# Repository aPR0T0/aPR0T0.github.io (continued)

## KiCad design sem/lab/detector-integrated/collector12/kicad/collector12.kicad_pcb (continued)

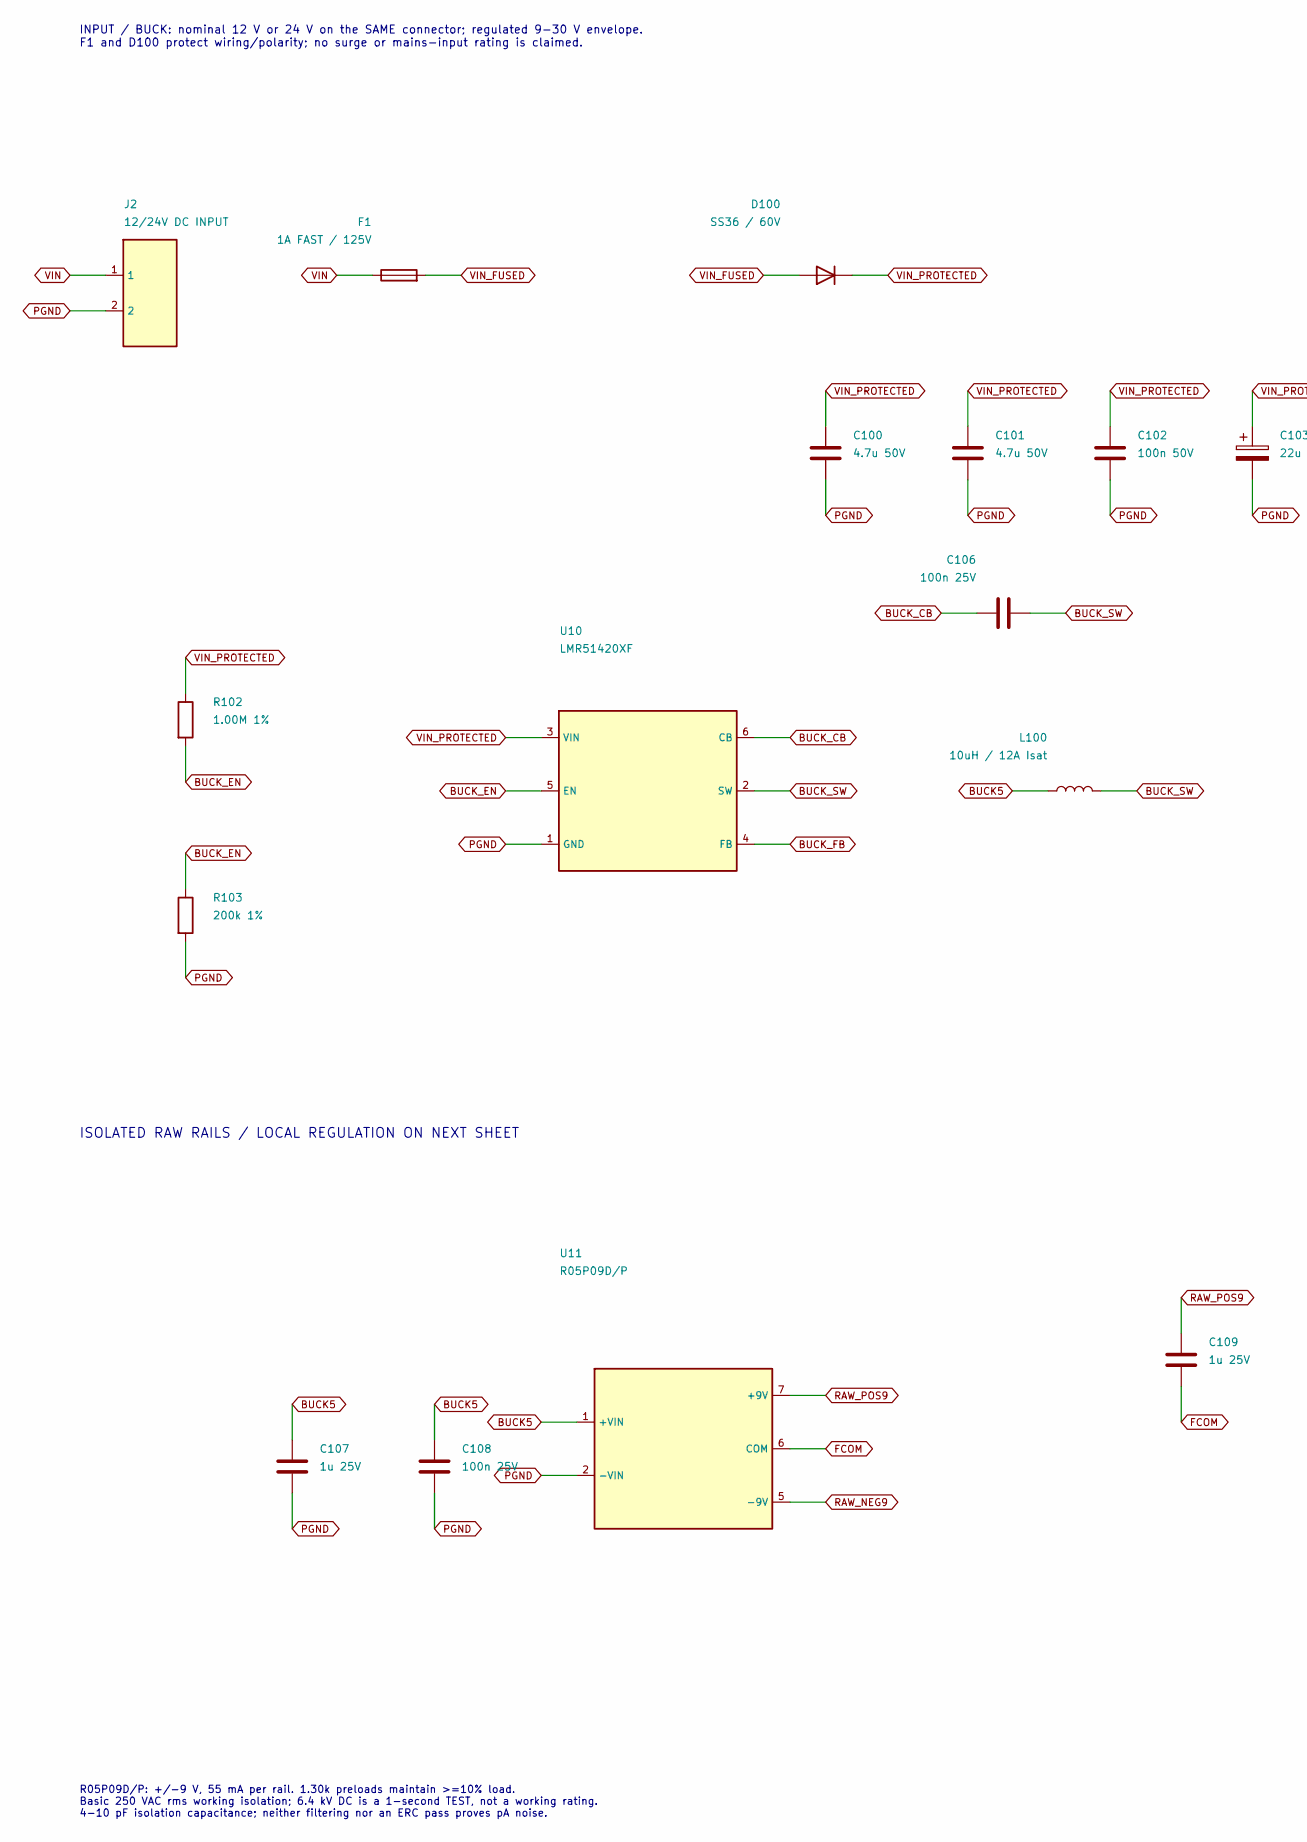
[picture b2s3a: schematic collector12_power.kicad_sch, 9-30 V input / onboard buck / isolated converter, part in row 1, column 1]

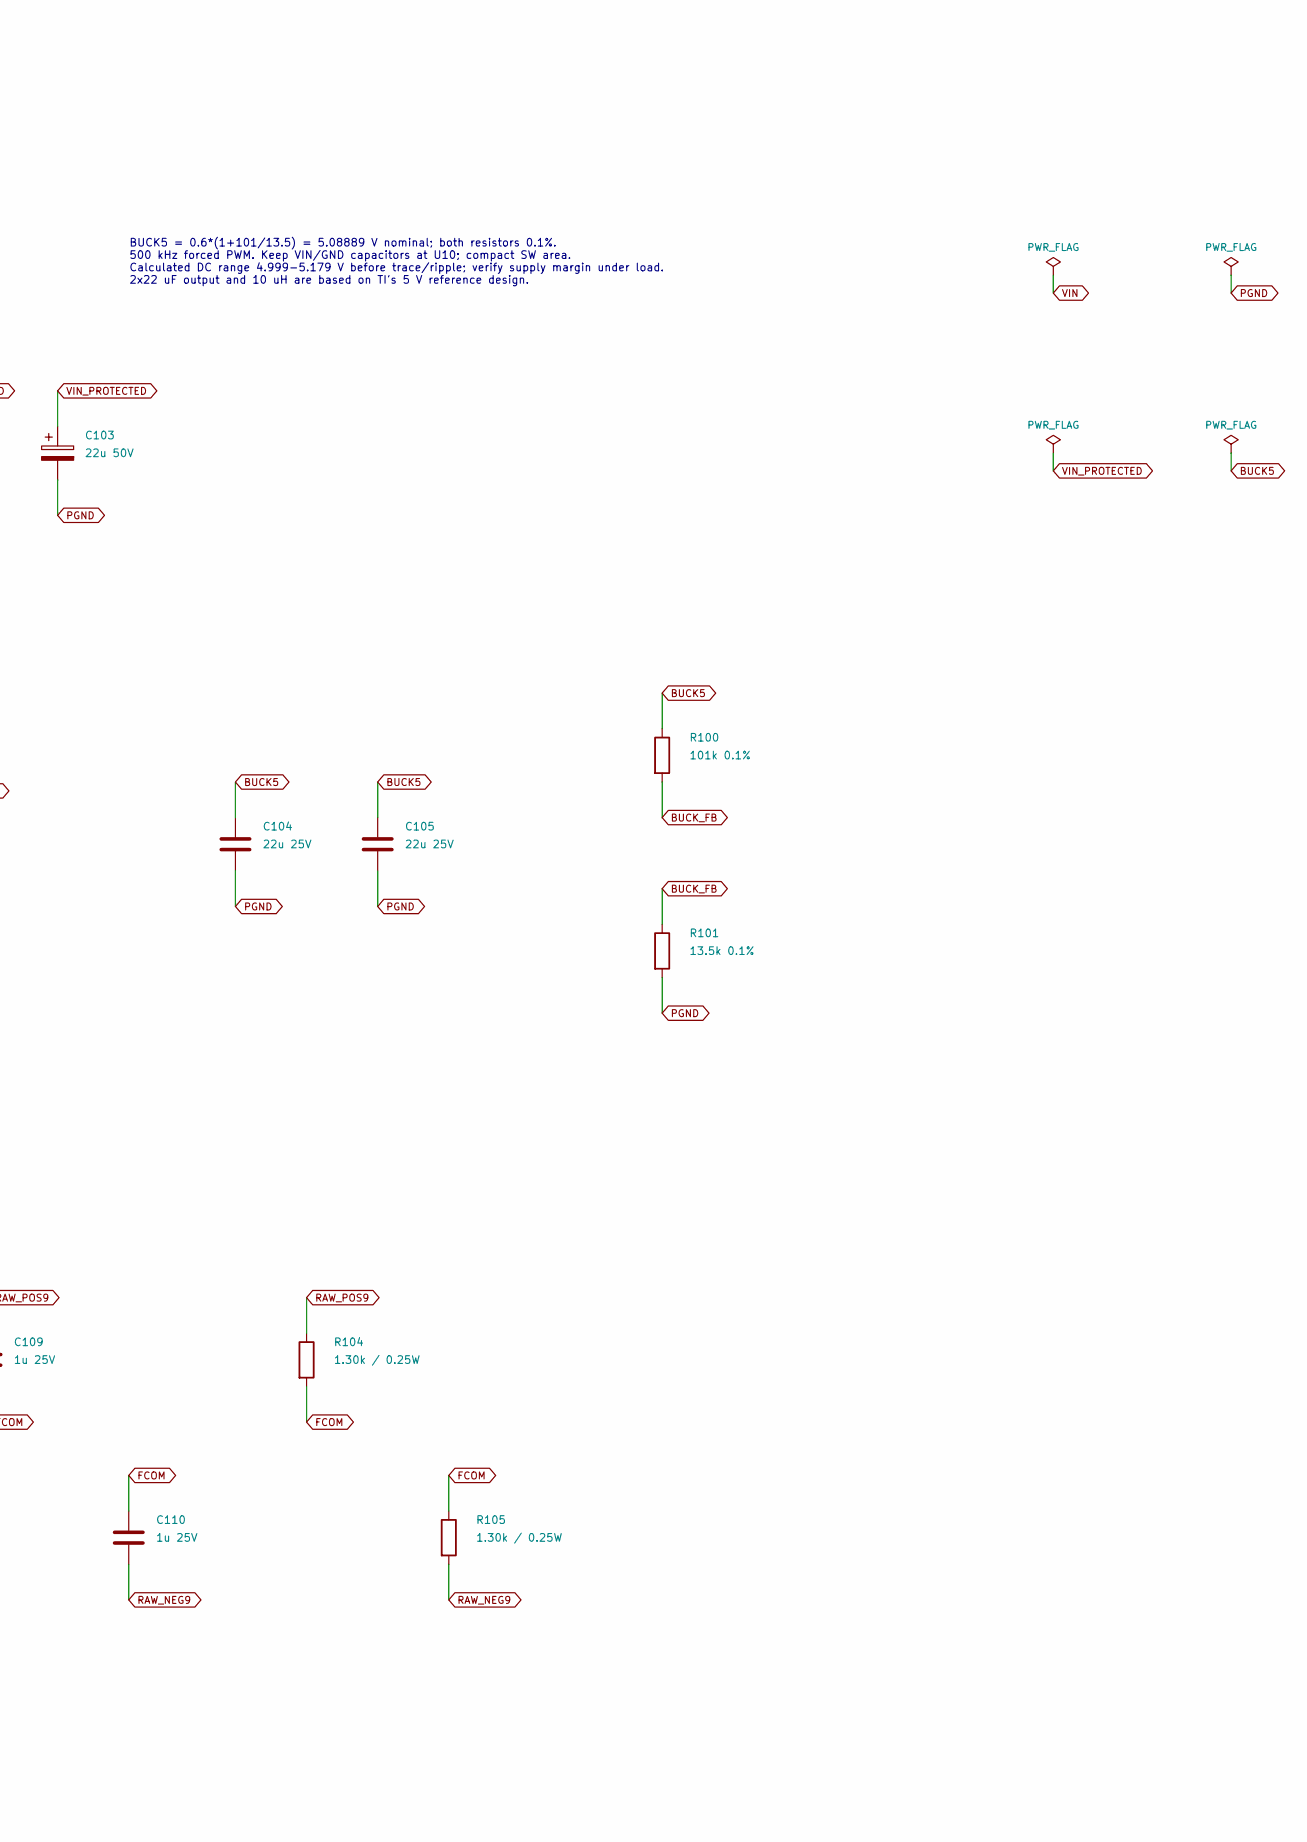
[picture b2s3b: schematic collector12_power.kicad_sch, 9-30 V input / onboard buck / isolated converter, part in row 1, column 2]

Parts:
C100, C101: 4.7u 50V; C_1210_3225Metric
C102: 100n 50V; C_0805_2012Metric
C103: 22u 50V; CP_Radial_D8.0mm_P3.50mm
C104, C105: 22u 25V; C_1210_3225Metric
C106, C108: 100n 25V; C_0805_2012Metric
C107, C109, C110: 1u 25V; C_0805_2012Metric
D100: SS36 / 60V; D_SMC; MPN SS36-E3/57T
F1: 1A FAST / 125V; Fuse_Littelfuse-NANO2-451_453; MPN 0451001.MRL
J2: 12/24V DC INPUT; PinHeader_1x02_P2.54mm_Vertical
L100: 10uH / 12A Isat; Bourns_SRP1038A; MPN SRP1038A-100M
R100: 101k 0.1%; R_0805_2012Metric
R101: 13.5k 0.1%; R_0805_2012Metric
R102: 1.00M 1%; R_0805_2012Metric
R103: 200k 1%; R_0805_2012Metric
R104, R105: 1.30k / 0.25W; R_1206_3216Metric
U10: LMR51420XF; SOT-23-6; MPN LMR51420XFDDCR
U11: R05P09D/P; R05P09D_SIP7; MPN R05P09D/P

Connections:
BUCK5: C104.1, C105.1, C107.1, C108.1, L100.1, R100.1, U11.1 (+VIN); also elsewhere on the board
BUCK_CB: C106.1, U10.6 (CB)
BUCK_EN: R102.2, R103.1, U10.5 (EN)
BUCK_FB: R100.2, R101.1, U10.4 (FB)
BUCK_SW: C106.2, L100.2, U10.2 (SW)
FCOM: C109.2, C110.1, R104.2, R105.1, U11.6 (COM); also elsewhere on the board
PGND: C100.2, C101.2, C102.2, C103.2, C104.2, C105.2, C107.2, C108.2, J2.2, R101.2, R103.2, U10.1 (GND), U11.2 (-VIN); also elsewhere on the board
RAW_NEG9: C110.2, R105.2, U11.5 (-9V); also elsewhere on the board
RAW_POS9: C109.1, R104.1, U11.7 (+9V); also elsewhere on the board
VIN: F1.1, J2.1
VIN_FUSED: D100.2 (A), F1.2
VIN_PROTECTED: C100.1, C101.1, C102.1, C103.1, D100.1 (K), R102.1, U10.3 (VIN)

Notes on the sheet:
INPUT / BUCK: nominal 12 V or 24 V on the SAME connector; regulated 9-30 V envelope. F1 and D100 protect wiring/polarity; no surge or mains-input rating is claimed.
BUCK5 = 0.6*(1+101/13.5) = 5.08889 V nominal; both resistors 0.1%. 500 kHz forced PWM. Keep VIN/GND capacitors at U10; compact SW area. Calculated DC range 4.999-5.179 V before trace/ripple; verify supply margin under load. 2x22 uF output and 10 uH are based on TI's 5 V reference design.
ISOLATED RAW RAILS / LOCAL REGULATION ON NEXT SHEET
R05P09D/P: +/-9 V, 55 mA per rail. 1.30k preloads maintain >=10% load. Basic 250 VAC rms working isolation; 6.4 kV DC is a 1-second TEST, not a working rating. 4-10 pF isolation capacitance; neither filtering nor an ERC pass proves pA noise.

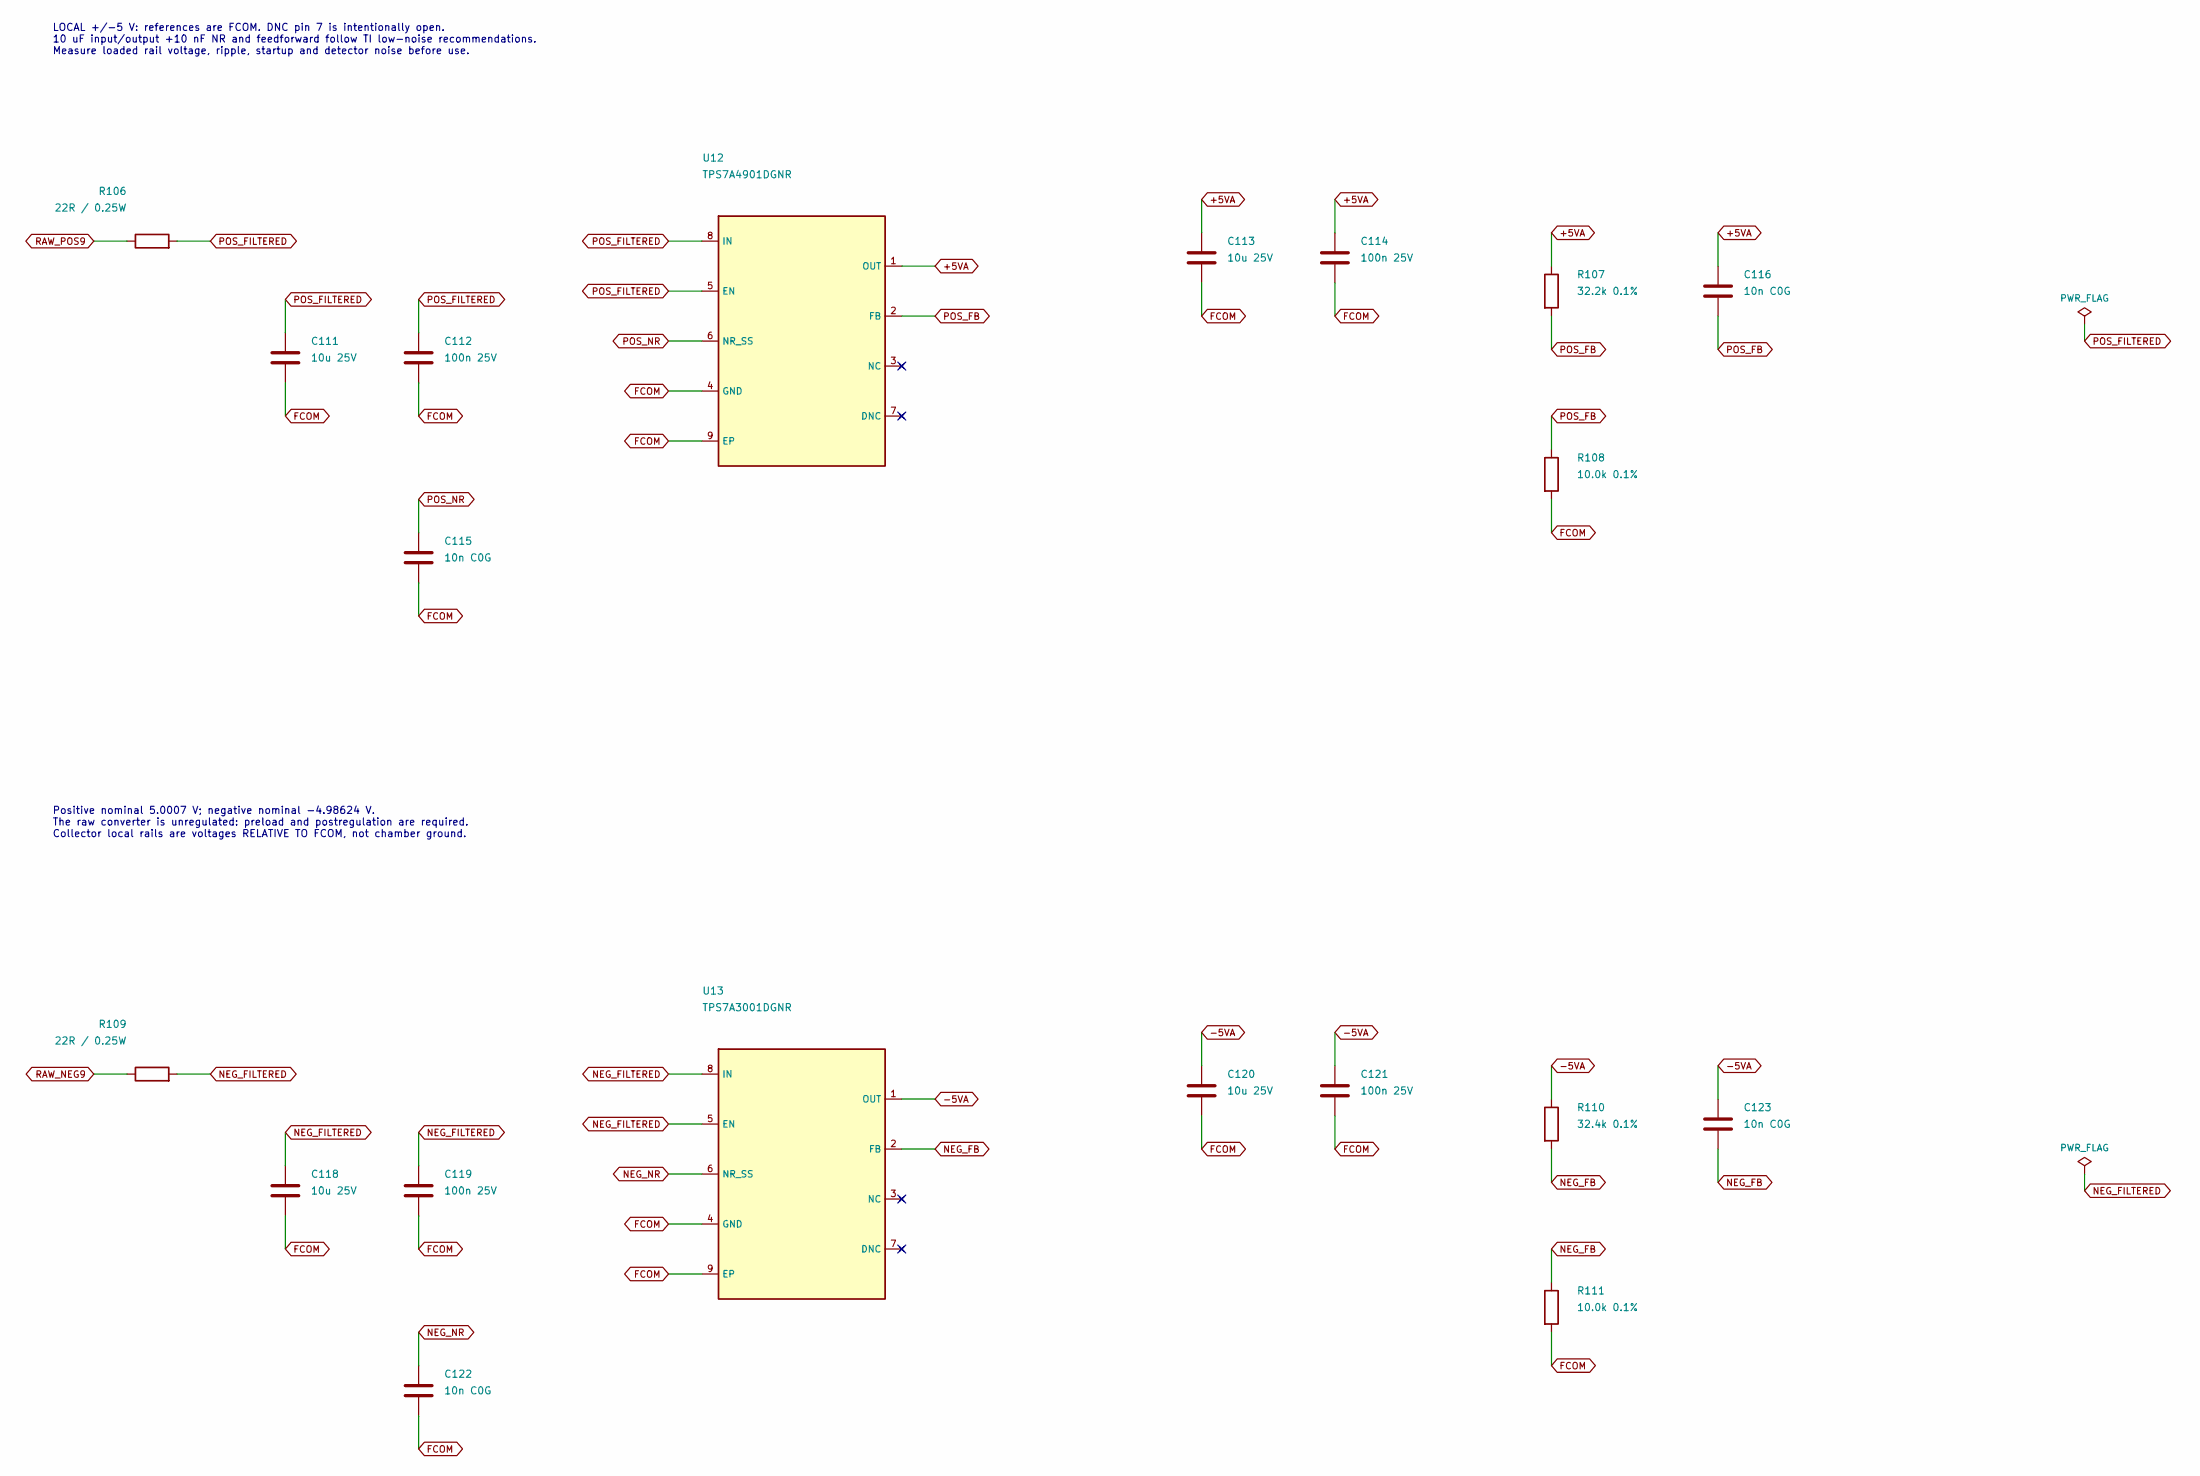
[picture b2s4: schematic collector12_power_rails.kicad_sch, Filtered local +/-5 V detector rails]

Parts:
C111, C113, C118, C120: 10u 25V; C_1210_3225Metric
C112, C114, C119, C121: 100n 25V; C_0805_2012Metric
C115, C116, C122, C123: 10n C0G; C_0805_2012Metric
R106, R109: 22R / 0.25W; R_1206_3216Metric
R107: 32.2k 0.1%; R_0805_2012Metric
R108, R111: 10.0k 0.1%; R_0805_2012Metric
R110: 32.4k 0.1%; R_0805_2012Metric
U12: TPS7A4901DGNR; TPS7A_DGN8_TI; MPN TPS7A4901DGNR
U13: TPS7A3001DGNR; TPS7A_DGN8_TI; MPN TPS7A3001DGNR

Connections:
+5VA: C113.1, C114.1, C116.1, R107.1, U12.1 (OUT); also elsewhere on the board
-5VA: C120.1, C121.1, C123.1, R110.1, U13.1 (OUT); also elsewhere on the board
FCOM: C111.2, C112.2, C113.2, C114.2, C115.2, C118.2, C119.2, C120.2, C121.2, C122.2, R108.2, R111.2, U12.4 (GND), U12.9 (EP), U13.4 (GND), U13.9 (EP); also elsewhere on the board
NEG_FB: C123.2, R110.2, R111.1, U13.2 (FB)
NEG_FILTERED: C118.1, C119.1, R109.2, U13.5 (EN), U13.8 (IN)
NEG_NR: C122.1, U13.6 (NR_SS)
POS_FB: C116.2, R107.2, R108.1, U12.2 (FB)
POS_FILTERED: C111.1, C112.1, R106.2, U12.5 (EN), U12.8 (IN)
POS_NR: C115.1, U12.6 (NR_SS)
RAW_NEG9: R109.1; also elsewhere on the board
RAW_POS9: R106.1; also elsewhere on the board

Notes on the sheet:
LOCAL +/-5 V: references are FCOM. DNC pin 7 is intentionally open. 10 uF input/output +10 nF NR and feedforward follow TI low-noise recommendations. Measure loaded rail voltage, ripple, startup and detector noise before use.
Positive nominal 5.0007 V; negative nominal -4.98624 V. The raw converter is unregulated: preload and postregulation are required. Collector local rails are voltages RELATIVE TO FCOM, not chamber ground.

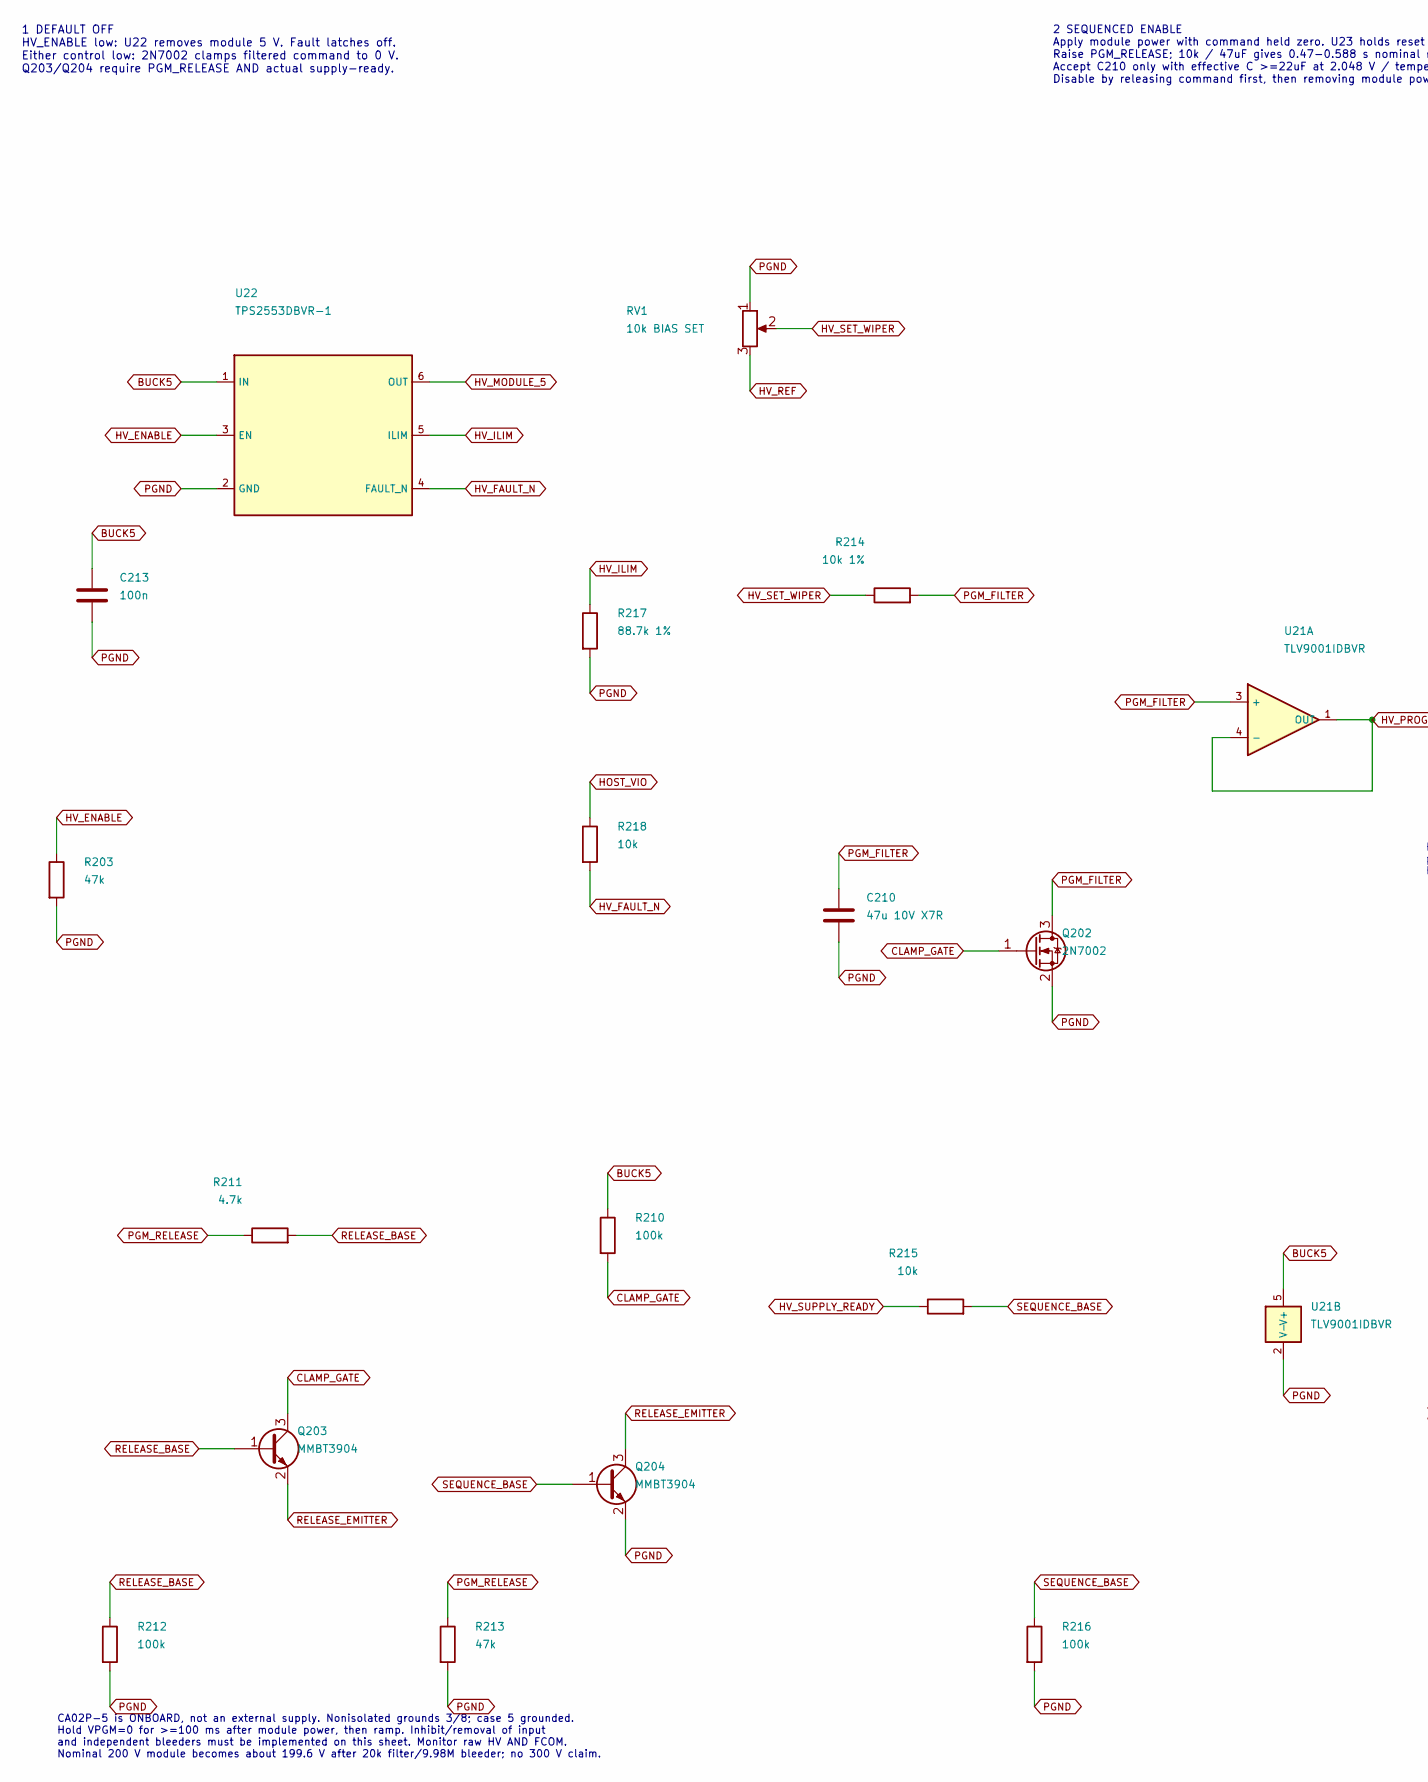
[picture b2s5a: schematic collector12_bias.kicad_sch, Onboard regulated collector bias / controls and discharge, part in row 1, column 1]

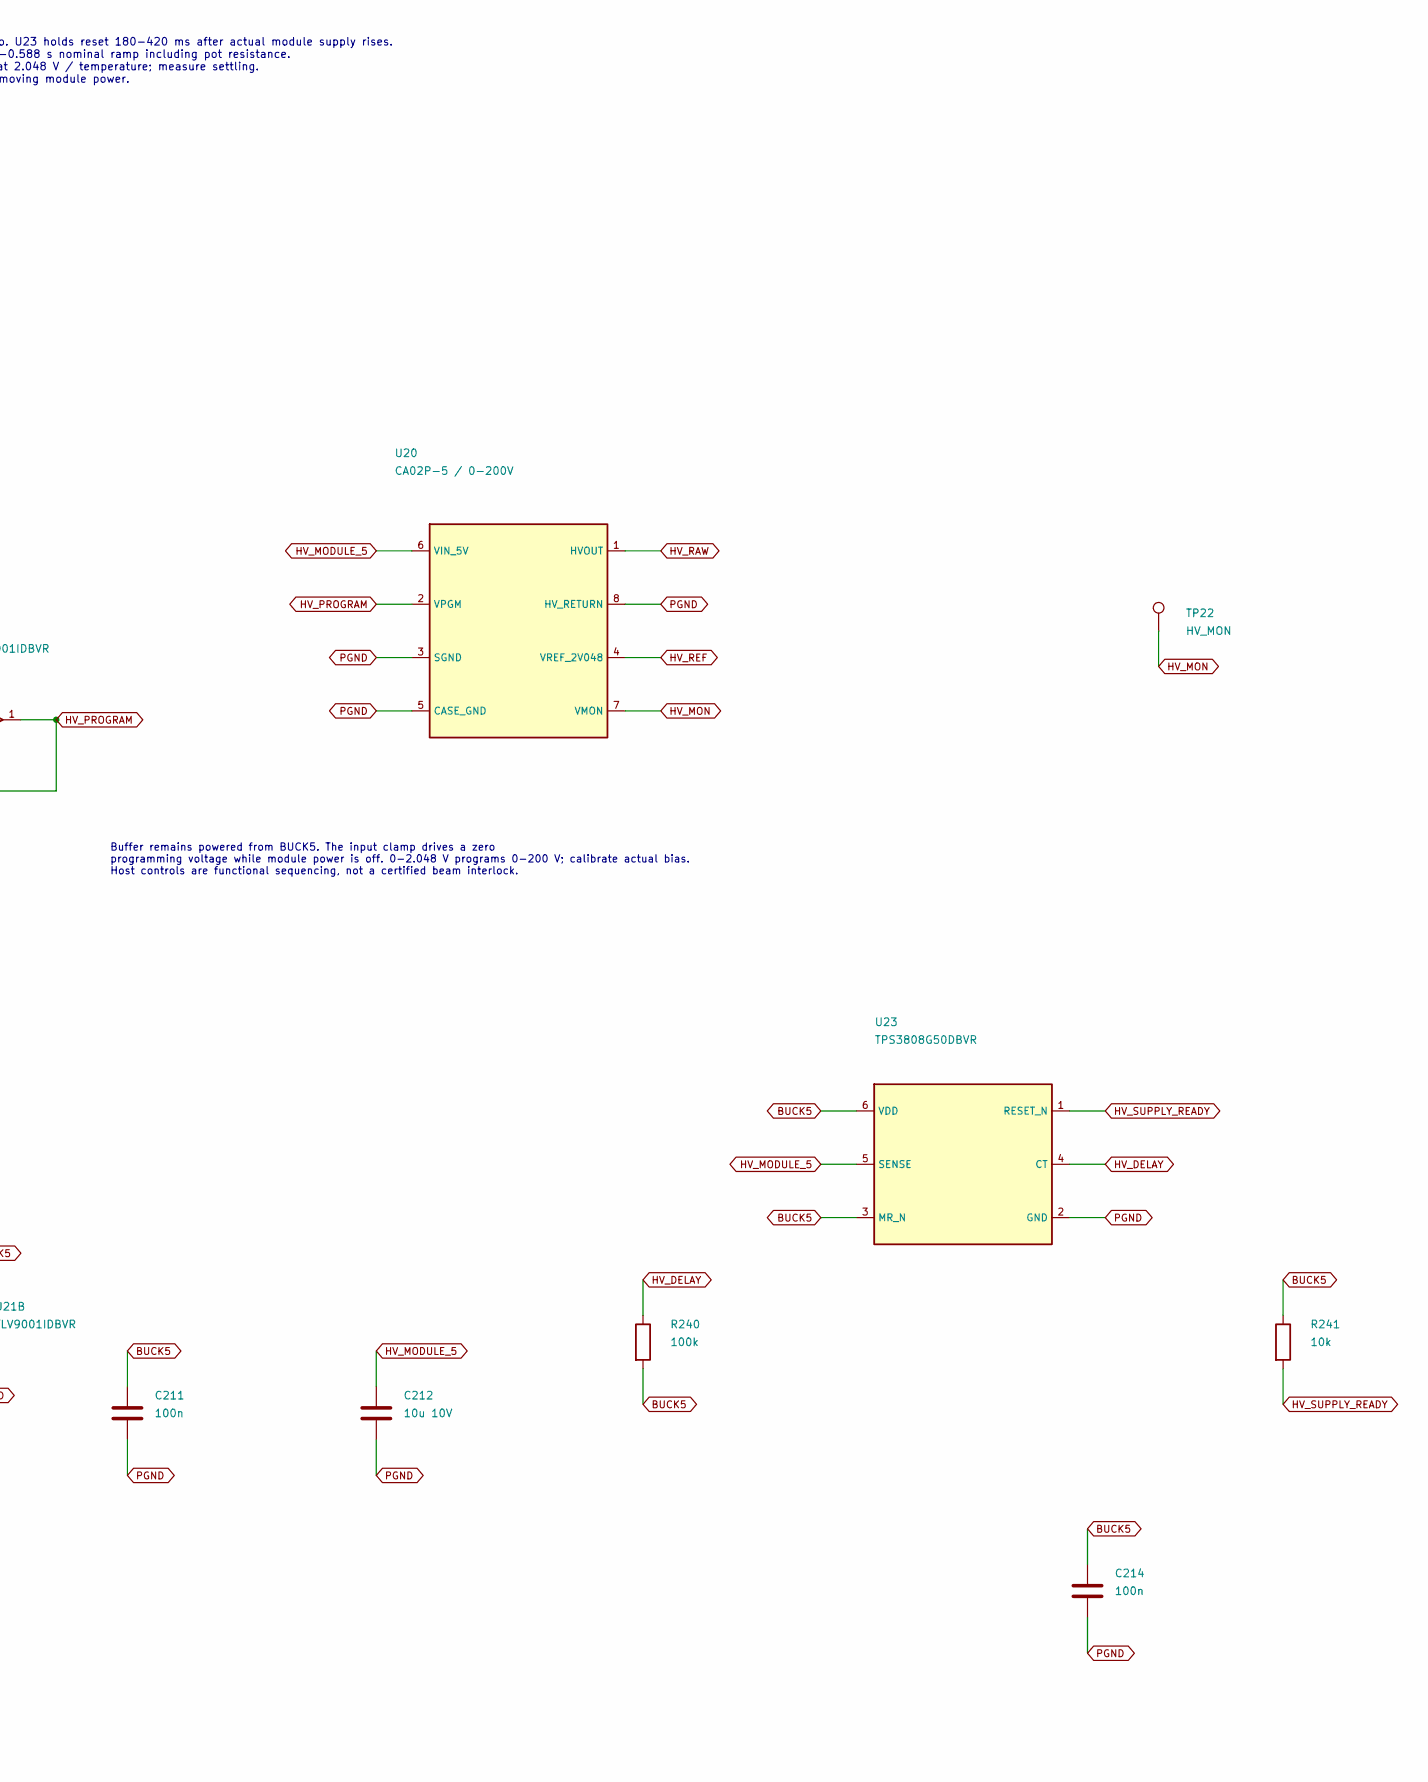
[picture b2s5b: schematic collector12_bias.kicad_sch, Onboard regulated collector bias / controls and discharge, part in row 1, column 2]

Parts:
C210: 47u 10V X7R; C_1210_3225Metric; MPN GRM32ER71A476KE15L
C211, C213, C214: 100n; C_0805_2012Metric
C212: 10u 10V; C_0805_2012Metric
Q202: 2N7002; SOT-23; MPN 2N7002
Q203, Q204: MMBT3904; SOT-23; MPN MMBT3904
R203, R213: 47k; R_0805_2012Metric
R210, R212, R216, R240: 100k; R_0805_2012Metric
R211: 4.7k; R_0805_2012Metric
R214: 10k 1%; R_0805_2012Metric
R215, R218, R241: 10k; R_0805_2012Metric
R217: 88.7k 1%; R_0805_2012Metric
RV1: 10k BIAS SET; Potentiometer_Bourns_3296W_Vertical; MPN 3296W-1-103LF
TP22: HV_MON; TestPoint_THTPad_D2.0mm_Drill1.0mm
U20: CA02P-5 / 0-200V; XP_CA02P5; MPN CA02P-5
U21: TLV9001IDBVR; SOT-23-5; MPN TLV9001IDBVR
U22: TPS2553DBVR-1; SOT-23-6; MPN TPS2553DBVR-1
U23: TPS3808G50DBVR; SOT-23-6; MPN TPS3808G50DBVR

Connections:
BUCK5: C211.1, C213.1, C214.1, R210.1, R240.2, R241.1, U21.5 (V+), U22.1 (IN), U23.3 (MR_N), U23.6 (VDD); also elsewhere on the board
CLAMP_GATE: Q202.1 (G), Q203.3 (C), R210.2
HOST_VIO: R218.1; also elsewhere on the board
HV_DELAY: R240.1, U23.4 (CT)
HV_ENABLE: R203.1, U22.3 (EN); also elsewhere on the board
HV_FAULT_N: R218.2, U22.4 (FAULT_N); also elsewhere on the board
HV_ILIM: R217.1, U22.5 (ILIM)
HV_MODULE_5: C212.1, U20.6 (VIN_5V), U22.6 (OUT), U23.5 (SENSE)
HV_MON: TP22.1, U20.7 (VMON)
HV_PROGRAM: U20.2 (VPGM), U21.1 (OUT), U21.4 (-)
HV_RAW: U20.1 (HVOUT); also elsewhere on the board
HV_REF: RV1.3, U20.4 (VREF_2V048)
HV_SET_WIPER: R214.1, RV1.2
HV_SUPPLY_READY: R215.1, R241.2, U23.1 (RESET_N)
PGM_FILTER: C210.1, Q202.3 (D), R214.2, U21.3 (+)
PGM_RELEASE: R211.1, R213.1; also elsewhere on the board
PGND: C210.2, C211.2, C212.2, C213.2, C214.2, Q202.2 (S), Q204.2 (E), R203.2, R212.2, R213.2, R216.2, R217.2, RV1.1, U20.3 (SGND), U20.5 (CASE_GND), U20.8 (HV_RETURN), U21.2 (V-), U22.2 (GND), U23.2 (GND); also elsewhere on the board
RELEASE_BASE: Q203.1 (B), R211.2, R212.1
RELEASE_EMITTER: Q203.2 (E), Q204.3 (C)
SEQUENCE_BASE: Q204.1 (B), R215.2, R216.1

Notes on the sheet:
CA02P-5 is ONBOARD, not an external supply. Nonisolated grounds 3/8; case 5 grounded. Hold VPGM=0 for >=100 ms after module power, then ramp. Inhibit/removal of input and independent bleeders must be implemented on this sheet. Monitor raw HV AND FCOM. Nominal 200 V module becomes about 199.6 V afte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
1 DEFAULT OFF HV_ENABLE low: U22 removes module 5 V. Fault latches off. Either control low: 2N7002 clamps filtered command to 0 V. Q203/Q204 require PGM_RELEASE AND actual supply-ready.
2 SEQUENCED ENABLE Apply module power with command held zero. U23 holds reset 180-420 ms after actual module supply rises. Raise PGM_RELEASE; 10k / 47uF gives 0.47-0.588 s nominal ramp including pot resistance. Accept C210 only with effective C >=22uF at 2.048 V / temperature; measure settling. Dis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
Buffer remains powered from BUCK5. The input clamp drives a zero programming voltage while module power is off. 0-2.048 V programs 0-200 V; calibrate actual bias. Host controls are functional sequencing, not a certified beam interlock.
